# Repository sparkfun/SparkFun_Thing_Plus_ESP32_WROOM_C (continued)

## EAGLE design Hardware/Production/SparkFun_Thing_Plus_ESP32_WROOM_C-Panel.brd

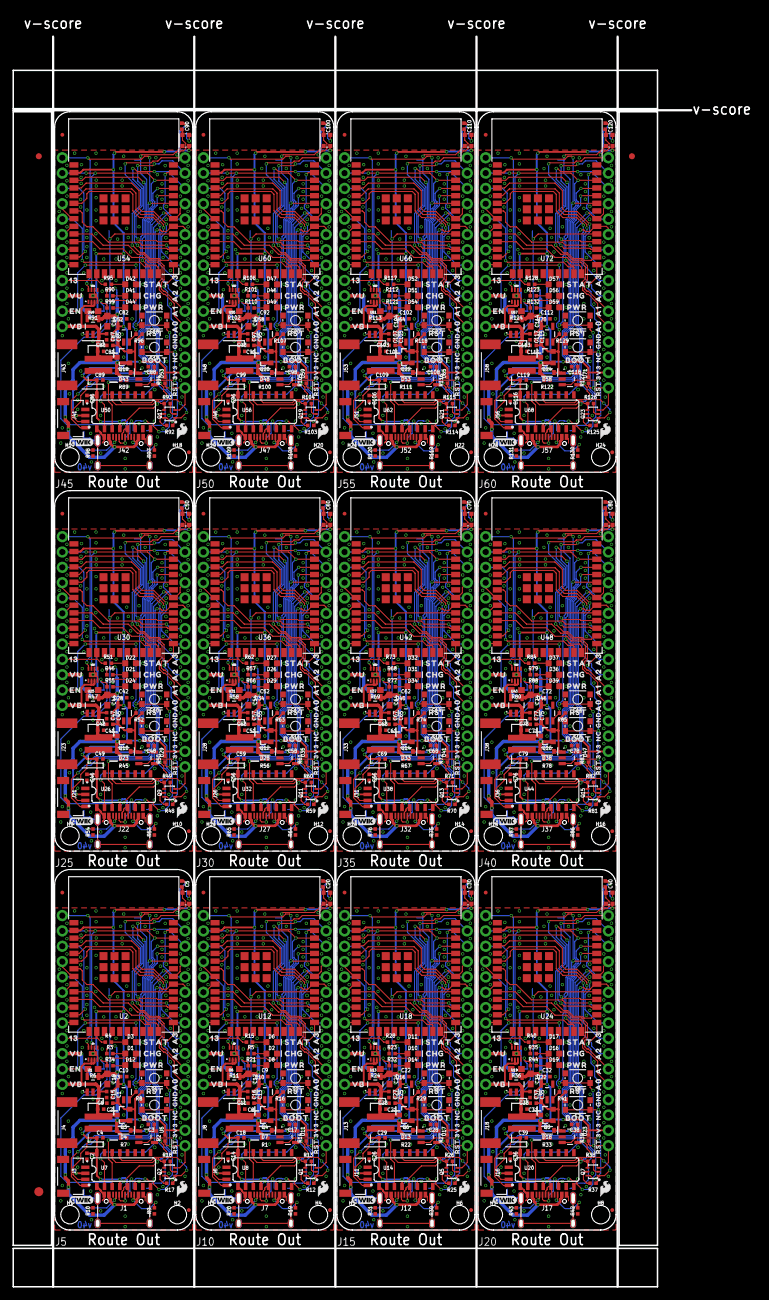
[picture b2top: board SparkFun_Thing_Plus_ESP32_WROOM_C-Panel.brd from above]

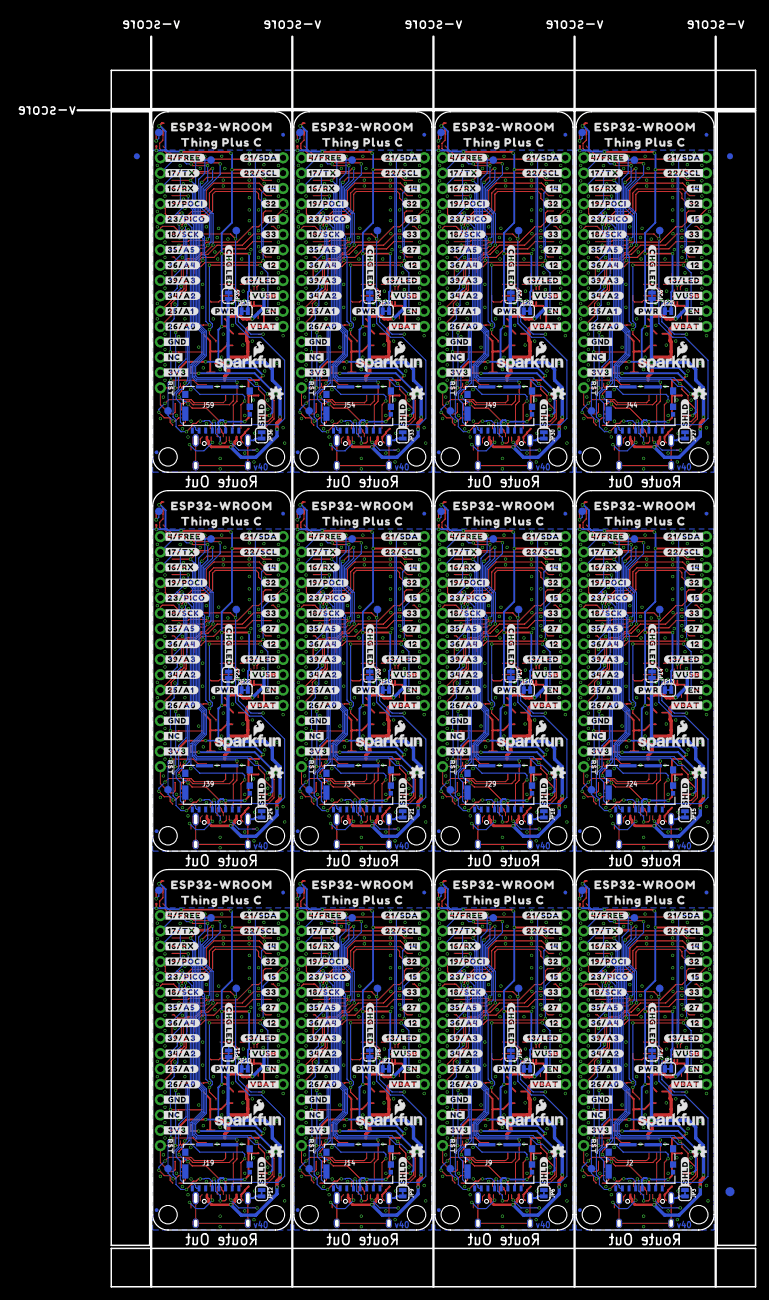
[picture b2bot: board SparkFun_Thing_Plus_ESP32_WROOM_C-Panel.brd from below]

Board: 2 copper layers, 112.3 x 207.0 mm, 1314 parts (555 on the bottom side), 612 nets.

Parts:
C1, C5, C13, C20, C25, C30, C35, C40, C45, C50, C55, C60, C65, C70, C75, C80, C85, C90, C95, C100, C105, C110, C115, C120: 10uF; 0402-TIGHT
C2, C4, C14, C15, C16, C18, C26, C27, C29, C36, C37, C39, C46, C47, C49, C56, C57, C59, C66, C67, C69, C76, C77, C79, C86, C87, C89, C96, C97, C99, C106, C107, C109, C116, C117, C119: 0.1uF; 0402-TIGHT
C3, C7, C8, C9, C10, C17, C21, C22, C28, C31, C32, C38, C41, C42, C48, C51, C52, C58, C61, C62, C68, C71, C72, C78, C81, C82, C88, C91, C92, C98, C101, C102, C108, C111, C112, C118: 1.0uF; 0402-TIGHT
C6, C11, C23, C33, C43, C53, C63, C73, C83, C93, C103, C113: 4.7uF; 0402-TIGHT
C12, C19, C24, C34, C44, C54, C64, C74, C84, C94, C104, C114: 4.7uF; 0603
D1, D2, D10, D16, D21, D26, D31, D36, D41, D46, D51, D56: Yellow; LED-0603
D3, D6, D11, D17, D22, D27, D32, D37, D42, D47, D52, D57: BLUE; LED-0603
D4, D7, D13, D18, D23, D28, D33, D38, D43, D48, D53, D58: 3A/10V/280mV; SOD-323
D5, D9, D15, D20, D25, D30, D35, D40, D45, D50, D55, D60: WS2812; WS2812-2020
D8, D12, D14, D19, D24, D29, D34, D39, D44, D49, D54, D59: RED; LED-0603
E$1, E$2, E$3, E$4: FIDUCIAL-1X2
E$5, E$6: FIDUCIAL-1.5X3
FD1, FD2, FD3, FD4, FD5, FD6, FD7, FD8, FD9, FD10, FD11, FD12, FD13, FD14, FD15, FD16, FD17, FD18, FD19, FD20, FD21, FD22, FD23, FD24, FD25, FD26, FD27, FD28, FD29, FD30, FD31, FD32, FD33, FD34, FD35, FD36, FD37, FD38, FD39, FD40, FD41, FD42, FD43, FD44, FD45, FD46, FD47, FD48: FIDUCIALUFIDUCIAL; FIDUCIAL-MICRO
H1, H2, H3, H4, H5, H6, H7, H8, H9, H10, H11, H12, H13, H14, H15, H16, H17, H18, H19, H20, H21, H22, H23, H24: STAND-OFFTIGHT; STAND-OFF-TIGHT
J1, J7, J12, J17, J22, J27, J32, J37, J42, J47, J52, J57: USB-C-16P-2LAYER-PADS
J2, J9, J14, J19, J24, J29, J34, J39, J44, J49, J54, J59: MICRO-SDFRICTION; MICROSD_TINY
J3, J6, J11, J16, J21, J26, J31, J36, J41, J46, J51, J56: QWIIC_RA; JST04_1MM_RA
J4, J8, J13, J18, J23, J28, J33, J38, J43, J48, J53, J58: JST-2-SMD
J5, J10, J15, J20, J25, J30, J35, J40, J45, J50, J55, J60: THING_PLUS_LOGICAL; THING_PLUS
JP1, JP2, JP3, JP4, JP5, JP6, JP7, JP8, JP9, JP10, JP11, JP12, JP13, JP14, JP15, JP16, JP17, JP18, JP19, JP20, JP21, JP22, JP23, JP24, JP25, JP26, JP27, JP28, JP29, JP30, JP31, JP32, JP33, JP34, JP35, JP36: JUMPER-SMT_2_NC_TRACE_SILK; SMT-JUMPER_2_NC_TRACE_SILK
LOGO1, LOGO6, LOGO9, LOGO12, LOGO15, LOGO18, LOGO21, LOGO24, LOGO27, LOGO30, LOGO33, LOGO36: SFE_LOGO_NAME_FLAME.1_INCH; SFE_LOGO_NAME_FLAME_.1
LOGO2, LOGO3, LOGO7, LOGO10, LOGO13, LOGO16, LOGO19, LOGO22, LOGO25, LOGO28, LOGO31, LOGO34: OSHW-LOGOMINI; OSHW-LOGO-MINI
LOGO4, LOGO5, LOGO8, LOGO11, LOGO14, LOGO17, LOGO20, LOGO23, LOGO26, LOGO29, LOGO32, LOGO35: QWIIC_LOGO_4MM; QWIIC_4MM
Q1, Q2, Q5, Q7, Q9, Q11, Q13, Q15, Q17, Q19, Q21, Q23: MBT3904DW1T1; SC70-6
Q3, Q4, Q6, Q8, Q10, Q12, Q14, Q16, Q18, Q20, Q22, Q24: 20V/4.2A/52mΩ/1.4W; SOT23-3
R1, R2, R7, R8, R12, R13, R14, R16, R17, R18, R22, R25, R26, R27, R29, R33, R37, R38, R39, R41, R45, R48, R49, R50, R52, R56, R59, R60, R61, R63, R67, R70, R71, R72, R74, R78, R81, R82, R83, R85, R89, R92, R93, R94, R96, R100, R103, R104, R105, R107, R111, R114, R115, R116, R118, R122, R125, R126, R127, R129: 10k; 0402-TIGHT
R3, R4, R5, R15, R21, R23, R28, R32, R34, R35, R40, R44, R46, R51, R55, R57, R62, R66, R68, R73, R77, R79, R84, R88, R90, R95, R99, R101, R106, R110, R112, R117, R121, R123, R128, R132: 1k; 0402-TIGHT
R6, R11, R24, R36, R47, R58, R69, R80, R91, R102, R113, R124: 2.0k; 0603
R9, R10, R19, R20, R30, R31, R42, R43, R53, R54, R64, R65, R75, R76, R86, R87, R97, R98, R108, R109, R119, R120, R130, R131: 5.1k; 0402-TIGHT
S1, S3, S5, S7, S9, S11, S13, S15, S17, S19, S21, S23: Boot; TACTILE_SWITCH_SMD_4.6X2.8MM
S2, S4, S6, S8, S10, S12, S14, S16, S18, S20, S22, S24: Reset; TACTILE_SWITCH_SMD_4.6X2.8MM
TP1, TP2, TP3, TP4, TP5, TP6, TP7, TP8, TP9, TP10, TP11, TP12, TP13, TP14, TP15, TP16, TP17, TP18, TP19, TP20, TP21, TP22, TP23, TP24, TP25, TP26, TP27, TP28, TP29, TP30, TP31, TP32, TP33, TP34, TP35, TP36, TP37, TP38, TP39, TP40, TP41, TP42, TP43, TP44, TP45, TP46, TP47, TP48: TEST-POINT3X5; PAD.03X.05
U1, U6, U13, U19, U25, U31, U37, U43, U49, U55, U61, U67: MCP73831; SOT23-5
U2, U12, U18, U24, U30, U36, U42, U48, U54, U60, U66, U72: ESP-WROOM-3232D-NARROW; ESP-WROOM-32D-NARROW
U3, U5, U10, U11, U16, U17, U22, U23, U28, U29, U34, U35, U40, U41, U46, U47, U52, U53, U58, U59, U64, U65, U70, U71: XC6222B331MR-G; SOT23-5
U4, U9, U15, U21, U27, U33, U39, U45, U51, U57, U63, U69: MAX17048; DFN-8
U7, U8, U14, U20, U26, U32, U38, U44, U50, U56, U62, U68: CH340C; SO016
U$1, U$57, U$145, U$197, U$249, U$301, U$353, U$405, U$457, U$509, U$561, U$613: SFE_LOGO_FLAME_STOP_.1
U$2, U$58, U$146, U$198, U$250, U$302, U$354, U$406, U$458, U$510, U$562, U$614: #23#PICO#0
U$3, U$59, U$147, U$199, U$251, U$303, U$355, U$407, U$459, U$511, U$563, U$615: #19#POCI#0
U$4, U$60, U$148, U$200, U$252, U$304, U$356, U$408, U$460, U$512, U$564, U$616: #4#FREE#0
U$5, U$61, U$149, U$201, U$253, U$305, U$357, U$409, U$461, U$513, U$565, U$617: #CHG_LED#0
U$6, U$62, U$150, U$202, U$254, U$306, U$358, U$410, U$462, U$514, U$566, U$618: ESP32#WROOM0
U$7, U$63, U$151, U$203, U$255, U$307, U$359, U$411, U$463, U$515, U$567, U$619: THING_PLUS_C0
U$8, U$82, U$156, U$208, U$260, U$312, U$364, U$416, U$468, U$520, U$572, U$624: #SHLD#0
U$9, U$64, U$152, U$204, U$256, U$308, U$360, U$412, U$464, U$516, U$568, U$620: #_GND#0
U$10, U$65, U$153, U$205, U$257, U$309, U$361, U$413, U$465, U$517, U$569, U$621: #_NC#0
U$11, U$66, U$154, U$206, U$258, U$310, U$362, U$414, U$466, U$518, U$570, U$622: #_3V3#0
U$12, U$67, U$155, U$207, U$259, U$311, U$363, U$415, U$467, U$519, U$571, U$623: SFE_LOGO_FLAME_.1
U$13, U$24, U$103, U$157, U$209, U$261, U$313, U$365, U$417, U$469, U$521, U$573: CHG1
U$14, U$25, U$104, U$158, U$210, U$262, U$314, U$366, U$418, U$470, U$522, U$574: PWR2
U$15, U$26, U$105, U$159, U$211, U$263, U$315, U$367, U$419, U$471, U$523, U$575: STAT0
U$16, U$68, U$106, U$160, U$212, U$264, U$316, U$368, U$420, U$472, U$524, U$576: A03
U$17, U$69, U$108, U$161, U$213, U$265, U$317, U$369, U$421, U$473, U$525, U$577: A12
U$18, U$70, U$110, U$162, U$214, U$266, U$318, U$370, U$422, U$474, U$526, U$578: A21
U$19, U$71, U$111, U$163, U$215, U$267, U$319, U$371, U$423, U$475, U$527, U$579: A30
U$20, U$74, U$112, U$164, U$216, U$268, U$320, U$372, U$424, U$476, U$528, U$580: EN3
U$21, U$77, U$113, U$165, U$217, U$269, U$321, U$373, U$425, U$477, U$529, U$581: 130
U$22, U$78, U$114, U$166, U$218, U$270, U$322, U$374, U$426, U$478, U$530, U$582: BOOT0
U$23, U$31, U$119, U$171, U$223, U$275, U$327, U$379, U$431, U$483, U$535, U$587: 3V30
U$27, U$54, U$79, U$109, U$115, U$142, U$167, U$194, U$219, U$246, U$271, U$298, U$323, U$350, U$375, U$402, U$427, U$454, U$479, U$506, U$531, U$558, U$583, U$610: #RST#0
U$28, U$80, U$116, U$168, U$220, U$272, U$324, U$376, U$428, U$480, U$532, U$584: RST0
U$29, U$73, U$117, U$169, U$221, U$273, U$325, U$377, U$429, U$481, U$533, U$585: VB1
U$30, U$76, U$118, U$170, U$222, U$274, U$326, U$378, U$430, U$482, U$534, U$586: VU0
U$32, U$72, U$120, U$172, U$224, U$276, U$328, U$380, U$432, U$484, U$536, U$588: #17#TX#0
U$33, U$81, U$121, U$173, U$225, U$277, U$329, U$381, U$433, U$485, U$537, U$589: #16#RX#0
U$34, U$83, U$122, U$174, U$226, U$278, U$330, U$382, U$434, U$486, U$538, U$590: #18#SCK#0
U$35, U$84, U$123, U$175, U$227, U$279, U$331, U$383, U$435, U$487, U$539, U$591: #35#A5#0
U$36, U$85, U$124, U$176, U$228, U$280, U$332, U$384, U$436, U$488, U$540, U$592: #36#A4#0
U$37, U$86, U$125, U$177, U$229, U$281, U$333, U$385, U$437, U$489, U$541, U$593: #25#A1#2
U$38, U$87, U$126, U$178, U$230, U$282, U$334, U$386, U$438, U$490, U$542, U$594: #26#A0#3
U$39, U$88, U$127, U$179, U$231, U$283, U$335, U$387, U$439, U$491, U$543, U$595: #34#A2#1
U$40, U$89, U$128, U$180, U$232, U$284, U$336, U$388, U$440, U$492, U$544, U$596: #39#A3#0
U$41, U$90, U$129, U$181, U$233, U$285, U$337, U$389, U$441, U$493, U$545, U$597: #12#4
U$42, U$91, U$130, U$182, U$234, U$286, U$338, U$390, U$442, U$494, U$546, U$598: #14#9
U$43, U$92, U$131, U$183, U$235, U$287, U$339, U$391, U$443, U$495, U$547, U$599: #15#7
U$44, U$93, U$132, U$184, U$236, U$288, U$340, U$392, U$444, U$496, U$548, U$600: #27#5
U$45, U$94, U$133, U$185, U$237, U$289, U$341, U$393, U$445, U$497, U$549, U$601: #32#8
U$46, U$95, U$134, U$186, U$238, U$290, U$342, U$394, U$446, U$498, U$550, U$602: #33#6
U$47, U$96, U$135, U$187, U$239, U$291, U$343, U$395, U$447, U$499, U$551, U$603: #EN#1
U$48, U$97, U$136, U$188, U$240, U$292, U$344, U$396, U$448, U$500, U$552, U$604: #VBAT#0
U$49, U$98, U$137, U$189, U$241, U$293, U$345, U$397, U$449, U$501, U$553, U$605: #VUSB#2
U$50, U$99, U$138, U$190, U$242, U$294, U$346, U$398, U$450, U$502, U$554, U$606: #13#LED#0
U$51, U$100, U$139, U$191, U$243, U$295, U$347, U$399, U$451, U$503, U$555, U$607: #21#SDA#1
U$52, U$101, U$140, U$192, U$244, U$296, U$348, U$400, U$452, U$504, U$556, U$608: #22#SCL#0
U$53, U$102, U$141, U$193, U$245, U$297, U$349, U$401, U$453, U$505, U$557, U$609: #PWR#0
U$55, U$75, U$143, U$195, U$247, U$299, U$351, U$403, U$455, U$507, U$559, U$611: GND1
U$56, U$107, U$144, U$196, U$248, U$300, U$352, U$404, U$456, U$508, U$560, U$612: NC0

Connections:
3.3V: C1.1, C2.1, C4.1, C5.1, C10.1, D5.VCC, J2.4, J5.27, JP1.2, R2.2, U2.2, U3.5, U7.4, U7.16
3.3V1: C9.1, C13.1, C14.1, C18.1, C20.1, D9.VCC, J9.4, J10.27, JP4.2, R14.2, U8.4, U8.16, U10.5, U12.2
3.3V2: C22.1, C25.1, C26.1, C29.1, C30.1, D15.VCC, J14.4, J15.27, JP7.2, R27.2, U14.4, U14.16, U16.5, U18.2
3.3V3: C32.1, C35.1, C36.1, C39.1, C40.1, D20.VCC, J19.4, J20.27, JP10.2, R39.2, U20.4, U20.16, U22.5, U24.2
3.3V4: C42.1, C45.1, C46.1, C49.1, C50.1, D25.VCC, J24.4, J25.27, JP13.2, R50.2, U26.4, U26.16, U28.5, U30.2
3.3V5: C52.1, C55.1, C56.1, C59.1, C60.1, D30.VCC, J29.4, J30.27, JP16.2, R61.2, U32.4, U32.16, U34.5, U36.2
3.3V6: C62.1, C65.1, C66.1, C69.1, C70.1, D35.VCC, J34.4, J35.27, JP19.2, R72.2, U38.4, U38.16, U40.5, U42.2
3.3V7: C72.1, C75.1, C76.1, C79.1, C80.1, D40.VCC, J39.4, J40.27, JP22.2, R83.2, U44.4, U44.16, U46.5, U48.2
3.3V8: C82.1, C85.1, C86.1, C89.1, C90.1, D45.VCC, J44.4, J45.27, JP25.2, R94.2, U50.4, U50.16, U52.5, U54.2
3.3V9: C92.1, C95.1, C96.1, C99.1, C100.1, D50.VCC, J49.4, J50.27, JP28.2, R105.2, U56.4, U56.16, U58.5, U60.2
3.3V10: C102.1, C105.1, C106.1, C109.1, C110.1, D55.VCC, J54.4, J55.27, JP31.2, R116.2, U62.4, U62.16, U64.5, U66.2
3.3V11: C112.1, C115.1, C116.1, C119.1, C120.1, D60.VCC, J59.4, J60.27, JP34.2, R127.2, U68.4, U68.16, U70.5, U72.2
!RESET!: J5.28, Q2.3, R2.1, S4.3, S4.4, U2.3
!RESET!1: J10.28, Q1.3, R14.1, S2.3, S2.4, U12.3
!RESET!2: J15.28, Q5.3, R27.1, S6.3, S6.4, U18.3
!RESET!3: J20.28, Q7.3, R39.1, S8.3, S8.4, U24.3
!RESET!4: J25.28, Q9.3, R50.1, S10.3, S10.4, U30.3
!RESET!5: J30.28, Q11.3, R61.1, S12.3, S12.4, U36.3
!RESET!6: J35.28, Q13.3, R72.1, S14.3, S14.4, U42.3
!RESET!7: J40.28, Q15.3, R83.1, S16.3, S16.4, U48.3
!RESET!8: J45.28, Q17.3, R94.1, S18.3, S18.4, U54.3
!RESET!9: J50.28, Q19.3, R105.1, S20.3, S20.4, U60.3
!RESET!10: J55.28, Q21.3, R116.1, S22.3, S22.4, U66.3
!RESET!11: J60.28, Q23.3, R127.1, S24.3, S24.4, U72.3
CH340-DTR: Q2.1, R17.1, U7.13
CH340-DTR1: Q1.1, R12.1, U8.13
CH340-DTR2: Q5.1, R25.1, U14.13
CH340-DTR3: Q7.1, R37.1, U20.13
CH340-DTR4: Q9.1, R48.1, U26.13
CH340-DTR5: Q11.1, R59.1, U32.13
CH340-DTR6: Q13.1, R70.1, U38.13
CH340-DTR7: Q15.1, R81.1, U44.13
CH340-DTR8: Q17.1, R92.1, U50.13
CH340-DTR9: Q19.1, R103.1, U56.13
CH340-DTR10: Q21.1, R114.1, U62.13
CH340-DTR11: Q23.1, R125.1, U68.13
CH340-RTS: Q2.4, R18.1, U7.14
CH340-RTS1: Q1.4, R13.1, U8.14
CH340-RTS2: Q5.4, R26.1, U14.14
CH340-RTS3: Q7.4, R38.1, U20.14
CH340-RTS4: Q9.4, R49.1, U26.14
CH340-RTS5: Q11.4, R60.1, U32.14
CH340-RTS6: Q13.4, R71.1, U38.14
CH340-RTS7: Q15.4, R82.1, U44.14
CH340-RTS8: Q17.4, R93.1, U50.14
CH340-RTS9: Q19.4, R104.1, U56.14
CH340-RTS10: Q21.4, R115.1, U62.14
CH340-RTS11: Q23.4, R126.1, U68.14
CH340-RX: U2.35, U7.3
CH340-RX1: U8.3, U12.35
CH340-RX2: U14.3, U18.35
CH340-RX3: U20.3, U24.35
CH340-RX4: U26.3, U30.35
CH340-RX5: U32.3, U36.35
CH340-RX6: U38.3, U42.35
CH340-RX7: U44.3, U48.35
CH340-RX8: U50.3, U54.35
CH340-RX9: U56.3, U60.35
CH340-RX10: U62.3, U66.35
CH340-RX11: U68.3, U72.35
CH340-TX: U2.34, U7.2
CH340-TX1: U8.2, U12.34
CH340-TX2: U14.2, U18.34
CH340-TX3: U20.2, U24.34
CH340-TX4: U26.2, U30.34
CH340-TX5: U32.2, U36.34
CH340-TX6: U38.2, U42.34
CH340-TX7: U44.2, U48.34
CH340-TX8: U50.2, U54.34
CH340-TX9: U56.2, U60.34
CH340-TX10: U62.2, U66.34
CH340-TX11: U68.2, U72.34
CHG_LED: D1.A, R3.2
CHG_LED1: D2.A, R5.2
CHG_LED2: D10.A, R23.2
CHG_LED3: D16.A, R35.2
CHG_LED4: D21.A, R46.2
CHG_LED5: D26.A, R57.2
CHG_LED6: D31.A, R68.2
CHG_LED7: D36.A, R79.2
CHG_LED8: D41.A, R90.2
CHG_LED9: D46.A, R101.2
CHG_LED10: D51.A, R112.2
CHG_LED11: D56.A, R123.2
D+: J1.A6, J1.B6, U7.5
D+1: J7.A6, J7.B6, U8.5
D+2: J12.A6, J12.B6, U14.5
D+3: J17.A6, J17.B6, U20.5
D+4: J22.A6, J22.B6, U26.5
D+5: J27.A6, J27.B6, U32.5
D+6: J32.A6, J32.B6, U38.5
D+7: J37.A6, J37.B6, U44.5
D+8: J42.A6, J42.B6, U50.5
D+9: J47.A6, J47.B6, U56.5
D+10: J52.A6, J52.B6, U62.5
D+11: J57.A6, J57.B6, U68.5
D-: J1.A7, J1.B7, U7.6
D-1: J7.A7, J7.B7, U8.6
D-2: J12.A7, J12.B7, U14.6
D-3: J17.A7, J17.B7, U20.6
D-4: J22.A7, J22.B7, U26.6
D-5: J27.A7, J27.B7, U32.6
D-6: J32.A7, J32.B7, U38.6
D-7: J37.A7, J37.B7, U44.6
D-8: J42.A7, J42.B7, U50.6
D-9: J47.A7, J47.B7, U56.6
D-10: J52.A7, J52.B7, U62.6
D-11: J57.A7, J57.B7, U68.6
DTR-10K: Q2.5, R17.2
DTR-10K1: Q1.5, R12.2
DTR-10K2: Q5.5, R25.2
DTR-10K3: Q7.5, R37.2
DTR-10K4: Q9.5, R48.2
DTR-10K5: Q11.5, R59.2
DTR-10K6: Q13.5, R70.2
DTR-10K7: Q15.5, R81.2
DTR-10K8: Q17.5, R92.2
DTR-10K9: Q19.5, R103.2
DTR-10K10: Q21.5, R114.2
DTR-10K11: Q23.5, R125.2
ESP_0/QPWR: Q2.6, S3.3, S3.4, TP1.1, U2.25, U5.3
ESP_0/QPWR1: Q1.6, S1.3, S1.4, TP5.1, U11.3, U12.25
ESP_0/QPWR2: Q5.6, S5.3, S5.4, TP9.1, U17.3, U18.25
ESP_0/QPWR3: Q7.6, S7.3, S7.4, TP13.1, U23.3, U24.25
ESP_0/QPWR4: Q9.6, S9.3, S9.4, TP17.1, U29.3, U30.25
ESP_0/QPWR5: Q11.6, S11.3, S11.4, TP21.1, U35.3, U36.25
ESP_0/QPWR6: Q13.6, S13.3, S13.4, TP25.1, U41.3, U42.25
ESP_0/QPWR7: Q15.6, S15.3, S15.4, TP29.1, U47.3, U48.25
ESP_0/QPWR8: Q17.6, S17.3, S17.4, TP33.1, U53.3, U54.25
ESP_0/QPWR9: Q19.6, S19.3, S19.4, TP37.1, U59.3, U60.25
ESP_0/QPWR10: Q21.6, S21.3, S21.4, TP41.1, U65.3, U66.25
ESP_0/QPWR11: Q23.6, S23.3, S23.4, TP45.1, U71.3, U72.25
ESP_2/RGB_DI: D5.DI, TP3.1, U2.24
ESP_2/RGB_DI1: D9.DI, TP7.1, U12.24
ESP_2/RGB_DI2: D15.DI, TP11.1, U18.24
ESP_2/RGB_DI3: D20.DI, TP15.1, U24.24
ESP_2/RGB_DI4: D25.DI, TP19.1, U30.24
ESP_2/RGB_DI5: D30.DI, TP23.1, U36.24
ESP_2/RGB_DI6: D35.DI, TP27.1, U42.24
ESP_2/RGB_DI7: D40.DI, TP31.1, U48.24
ESP_2/RGB_DI8: D45.DI, TP35.1, U54.24
ESP_2/RGB_DI9: D50.DI, TP39.1, U60.24
ESP_2/RGB_DI10: D55.DI, TP43.1, U66.24
ESP_2/RGB_DI11: D60.DI, TP47.1, U72.24
ESP_4/TP_FB: J5.13, U2.26
ESP_4/TP_FB1: J10.13, U12.26
ESP_4/TP_FB2: J15.13, U18.26
ESP_4/TP_FB3: J20.13, U24.26
ESP_4/TP_FB4: J25.13, U30.26
ESP_4/TP_FB5: J30.13, U36.26
ESP_4/TP_FB6: J35.13, U42.26
ESP_4/TP_FB7: J40.13, U48.26
ESP_4/TP_FB8: J45.13, U54.26
ESP_4/TP_FB9: J50.13, U60.26
ESP_4/TP_FB10: J55.13, U66.26
ESP_4/TP_FB11: J60.13, U72.26
ESP_5/SD_CS: J2.2, TP4.1, U2.29
ESP_5/SD_CS1: J9.2, TP8.1, U12.29
ESP_5/SD_CS2: J14.2, TP12.1, U18.29
ESP_5/SD_CS3: J19.2, TP16.1, U24.29
ESP_5/SD_CS4: J24.2, TP20.1, U30.29
ESP_5/SD_CS5: J29.2, TP24.1, U36.29
ESP_5/SD_CS6: J34.2, TP28.1, U42.29
ESP_5/SD_CS7: J39.2, TP32.1, U48.29
ESP_5/SD_CS8: J44.2, TP36.1, U54.29
ESP_5/SD_CS9: J49.2, TP40.1, U60.29
ESP_5/SD_CS10: J54.2, TP44.1, U66.29
ESP_5/SD_CS11: J59.2, TP48.1, U72.29
ESP_12/GPIO1: J5.8, U2.14
ESP_12/GPIO2: J10.8, U12.14
ESP_12/GPIO3: J15.8, U18.14
ESP_12/GPIO4: J20.8, U24.14
ESP_12/GPIO5: J25.8, U30.14
ESP_12/GPIO6: J30.8, U36.14
ESP_12/GPIO7: J35.8, U42.14
ESP_12/GPIO8: J40.8, U48.14
ESP_12/GPIO9: J45.8, U54.14
ESP_12/GPIO10: J50.8, U60.14
ESP_12/GPIO11: J55.8, U66.14
ESP_12/GPIO12: J60.8, U72.14
ESP_13/GPIO0/LED: J5.9, R4.1, U2.16
ESP_13/GPIO0/LED1: J10.9, R15.1, U12.16
ESP_13/GPIO0/LED2: J15.9, R28.1, U18.16
ESP_13/GPIO0/LED3: J20.9, R40.1, U24.16
ESP_13/GPIO0/LED4: J25.9, R51.1, U30.16
ESP_13/GPIO0/LED5: J30.9, R62.1, U36.16
ESP_13/GPIO0/LED6: J35.9, R73.1, U42.16
ESP_13/GPIO0/LED7: J40.9, R84.1, U48.16
ESP_13/GPIO0/LED8: J45.9, R95.1, U54.16
ESP_13/GPIO0/LED9: J50.9, R106.1, U60.16
ESP_13/GPIO0/LED10: J55.9, R117.1, U66.16
ESP_13/GPIO0/LED11: J60.9, R128.1, U72.16
ESP_14/GPIO1: J10.3, U12.13
ESP_14/GPIO2: J15.3, U18.13
ESP_14/GPIO3: J20.3, U24.13
ESP_14/GPIO4: J25.3, U30.13
ESP_14/GPIO5: J30.3, U36.13
ESP_14/GPIO6: J5.3, U2.13
ESP_14/GPIO7: J35.3, U42.13
ESP_14/GPIO8: J40.3, U48.13
ESP_14/GPIO9: J45.3, U54.13
ESP_14/GPIO10: J50.3, U60.13
ESP_14/GPIO11: J55.3, U66.13
ESP_14/GPIO12: J60.3, U72.13
ESP_15/GPIO1: J10.5, U12.23
ESP_15/GPIO2: J15.5, U18.23
ESP_15/GPIO3: J20.5, U24.23
ESP_15/GPIO4: J5.5, U2.23
ESP_15/GPIO5: J25.5, U30.23
ESP_15/GPIO6: J30.5, U36.23
ESP_15/GPIO7: J35.5, U42.23
ESP_15/GPIO8: J40.5, U48.23
ESP_15/GPIO9: J45.5, U54.23
ESP_15/GPIO10: J50.5, U60.23
ESP_15/GPIO11: J55.5, U66.23
ESP_15/GPIO12: J60.5, U72.23
ESP_16/TP_RX: J5.15, U2.27
ESP_16/TP_RX1: J10.15, U12.27
ESP_16/TP_RX2: J15.15, U18.27
ESP_16/TP_RX3: J20.15, U24.27
ESP_16/TP_RX4: J25.15, U30.27
ESP_16/TP_RX5: J30.15, U36.27
ESP_16/TP_RX6: J35.15, U42.27
ESP_16/TP_RX7: J40.15, U48.27
ESP_16/TP_RX8: J45.15, U54.27
ESP_16/TP_RX9: J50.15, U60.27
ESP_16/TP_RX10: J55.15, U66.27
ESP_16/TP_RX11: J60.15, U72.27
ESP_17/TP_TX: J5.14, U2.28
ESP_17/TP_TX1: J10.14, U12.28
ESP_17/TP_TX2: J15.14, U18.28
ESP_17/TP_TX3: J20.14, U24.28
ESP_17/TP_TX4: J25.14, U30.28
ESP_17/TP_TX5: J30.14, U36.28
ESP_17/TP_TX6: J35.14, U42.28
ESP_17/TP_TX7: J40.14, U48.28
ESP_17/TP_TX8: J45.14, U54.28
ESP_17/TP_TX9: J50.14, U60.28
ESP_17/TP_TX10: J55.14, U66.28
ESP_17/TP_TX11: J60.14, U72.28
ESP_18/TP_SCK: J2.5, J5.18, U2.30
ESP_18/TP_SCK1: J9.5, J10.18, U12.30
ESP_18/TP_SCK2: J14.5, J15.18, U18.30
ESP_18/TP_SCK3: J19.5, J20.18, U24.30
ESP_18/TP_SCK4: J24.5, J25.18, U30.30
ESP_18/TP_SCK5: J29.5, J30.18, U36.30
ESP_18/TP_SCK6: J34.5, J35.18, U42.30
ESP_18/TP_SCK7: J39.5, J40.18, U48.30
ESP_18/TP_SCK8: J44.5, J45.18, U54.30
ESP_18/TP_SCK9: J49.5, J50.18, U60.30
ESP_18/TP_SCK10: J54.5, J55.18, U66.30
ESP_18/TP_SCK11: J59.5, J60.18, U72.30
ESP_19/TP_POCI: J2.7, J5.16, U2.31
ESP_19/TP_POCI1: J9.7, J10.16, U12.31
ESP_19/TP_POCI2: J14.7, J15.16, U18.31
ESP_19/TP_POCI3: J19.7, J20.16, U24.31
ESP_19/TP_POCI4: J24.7, J25.16, U30.31
ESP_19/TP_POCI5: J29.7, J30.16, U36.31
ESP_19/TP_POCI6: J34.7, J35.16, U42.31
ESP_19/TP_POCI7: J39.7, J40.16, U48.31
ESP_19/TP_POCI8: J44.7, J45.16, U54.31
ESP_19/TP_POCI9: J49.7, J50.16, U60.31
ESP_19/TP_POCI10: J54.7, J55.16, U66.31
ESP_19/TP_POCI11: J59.7, J60.16, U72.31
ESP_21/TP_SDA: J3.3, J5.1, U2.33, U4.8
ESP_21/TP_SDA1: J6.3, J10.1, U9.8, U12.33
ESP_21/TP_SDA2: J11.3, J15.1, U15.8, U18.33
ESP_21/TP_SDA3: J16.3, J20.1, U21.8, U24.33
ESP_21/TP_SDA4: J21.3, J25.1, U27.8, U30.33
ESP_21/TP_SDA5: J26.3, J30.1, U33.8, U36.33
ESP_21/TP_SDA6: J31.3, J35.1, U39.8, U42.33
ESP_21/TP_SDA7: J36.3, J40.1, U45.8, U48.33
ESP_21/TP_SDA8: J41.3, J45.1, U51.8, U54.33
ESP_21/TP_SDA9: J46.3, J50.1, U57.8, U60.33
ESP_21/TP_SDA10: J51.3, J55.1, U63.8, U66.33
ESP_21/TP_SDA11: J56.3, J60.1, U69.8, U72.33
ESP_22/TP_SCL: J3.4, J5.2, U2.36, U4.7
ESP_22/TP_SCL1: J6.4, J10.2, U9.7, U12.36
ESP_22/TP_SCL2: J11.4, J15.2, U15.7, U18.36
ESP_22/TP_SCL3: J16.4, J20.2, U21.7, U24.36
ESP_22/TP_SCL4: J21.4, J25.2, U27.7, U30.36
ESP_22/TP_SCL5: J26.4, J30.2, U33.7, U36.36
ESP_22/TP_SCL6: J31.4, J35.2, U39.7, U42.36
ESP_22/TP_SCL7: J36.4, J40.2, U45.7, U48.36
ESP_22/TP_SCL8: J41.4, J45.2, U51.7, U54.36
ESP_22/TP_SCL9: J46.4, J50.2, U57.7, U60.36
ESP_22/TP_SCL10: J51.4, J55.2, U63.7, U66.36
ESP_22/TP_SCL11: J56.4, J60.2, U69.7, U72.36
ESP_23/TP_PICO: J2.3, J5.17, U2.37
ESP_23/TP_PICO1: J9.3, J10.17, U12.37
ESP_23/TP_PICO2: J14.3, J15.17, U18.37
ESP_23/TP_PICO3: J19.3, J20.17, U24.37
ESP_23/TP_PICO4: J24.3, J25.17, U30.37
ESP_23/TP_PICO5: J29.3, J30.17, U36.37
ESP_23/TP_PICO6: J34.3, J35.17, U42.37
ESP_23/TP_PICO7: J39.3, J40.17, U48.37
ESP_23/TP_PICO8: J44.3, J45.17, U54.37
ESP_23/TP_PICO9: J49.3, J50.17, U60.37
ESP_23/TP_PICO10: J54.3, J55.17, U66.37
ESP_23/TP_PICO11: J59.3, J60.17, U72.37
ESP_25/TP_A1: J5.23, U2.10
ESP_25/TP_A2: J10.23, U12.10
ESP_25/TP_A3: J15.23, U18.10
ESP_25/TP_A4: J20.23, U24.10
ESP_25/TP_A5: J25.23, U30.10
ESP_25/TP_A6: J30.23, U36.10
ESP_25/TP_A7: J35.23, U42.10
ESP_25/TP_A8: J40.23, U48.10
ESP_25/TP_A9: J45.23, U54.10
ESP_25/TP_A10: J50.23, U60.10
ESP_25/TP_A11: J55.23, U66.10
ESP_25/TP_A12: J60.23, U72.10
ESP_26/TP_A0: J5.24, U2.11
ESP_26/TP_A1: J10.24, U12.11
ESP_26/TP_A2: J15.24, U18.11
ESP_26/TP_A3: J20.24, U24.11
ESP_26/TP_A4: J25.24, U30.11
ESP_26/TP_A5: J30.24, U36.11
ESP_26/TP_A6: J35.24, U42.11
ESP_26/TP_A7: J40.24, U48.11
ESP_26/TP_A8: J45.24, U54.11
ESP_26/TP_A9: J50.24, U60.11
ESP_26/TP_A10: J55.24, U66.11
ESP_26/TP_A11: J60.24, U72.11
ESP_27/GPIO1: J10.7, U12.12
ESP_27/GPIO2: J5.7, U2.12
ESP_27/GPIO3: J15.7, U18.12
ESP_27/GPIO4: J20.7, U24.12
ESP_27/GPIO5: J25.7, U30.12
ESP_27/GPIO6: J30.7, U36.12
ESP_27/GPIO7: J35.7, U42.12
ESP_27/GPIO8: J40.7, U48.12
ESP_27/GPIO9: J45.7, U54.12
ESP_27/GPIO10: J50.7, U60.12
ESP_27/GPIO11: J55.7, U66.12
ESP_27/GPIO12: J60.7, U72.12
ESP_32/GPIO1: J10.4, U12.8
ESP_32/GPIO2: J15.4, U18.8
ESP_32/GPIO3: J20.4, U24.8
ESP_32/GPIO4: J25.4, U30.8
ESP_32/GPIO5: J5.4, U2.8
ESP_32/GPIO6: J30.4, U36.8
ESP_32/GPIO7: J35.4, U42.8
ESP_32/GPIO8: J40.4, U48.8
ESP_32/GPIO9: J45.4, U54.8
ESP_32/GPIO10: J50.4, U60.8
ESP_32/GPIO11: J55.4, U66.8
ESP_32/GPIO12: J60.4, U72.8
ESP_33/GPIO1: J10.6, U12.9
ESP_33/GPIO2: J15.6, U18.9
ESP_33/GPIO3: J5.6, U2.9
ESP_33/GPIO4: J20.6, U24.9
ESP_33/GPIO5: J25.6, U30.9
ESP_33/GPIO6: J30.6, U36.9
ESP_33/GPIO7: J35.6, U42.9
ESP_33/GPIO8: J40.6, U48.9
ESP_33/GPIO9: J45.6, U54.9
ESP_33/GPIO10: J50.6, U60.9
ESP_33/GPIO11: J55.6, U66.9
ESP_33/GPIO12: J60.6, U72.9
ESP_34/TP_A1: J10.22, U12.6
ESP_34/TP_A2: J5.22, U2.6
ESP_34/TP_A3: J15.22, U18.6
ESP_34/TP_A4: J20.22, U24.6
ESP_34/TP_A5: J25.22, U30.6
ESP_34/TP_A6: J30.22, U36.6
ESP_34/TP_A7: J35.22, U42.6
ESP_34/TP_A8: J40.22, U48.6
ESP_34/TP_A9: J45.22, U54.6
ESP_34/TP_A10: J50.22, U60.6
ESP_34/TP_A11: J55.22, U66.6
ESP_34/TP_A12: J60.22, U72.6
ESP_35/TP_A1: J10.19, U12.7
ESP_35/TP_A2: J15.19, U18.7
ESP_35/TP_A3: J20.19, U24.7
ESP_35/TP_A4: J25.19, U30.7
ESP_35/TP_A5: J5.19, U2.7
ESP_35/TP_A6: J30.19, U36.7
ESP_35/TP_A7: J35.19, U42.7
ESP_35/TP_A8: J40.19, U48.7
ESP_35/TP_A9: J45.19, U54.7
ESP_35/TP_A10: J50.19, U60.7
ESP_35/TP_A11: J55.19, U66.7
ESP_35/TP_A12: J60.19, U72.7
ESP_36/TP_A1: J10.20, U12.4
ESP_36/TP_A2: J15.20, U18.4
ESP_36/TP_A3: J20.20, U24.4
ESP_36/TP_A4: J5.20, U2.4
ESP_36/TP_A5: J25.20, U30.4
ESP_36/TP_A6: J30.20, U36.4
ESP_36/TP_A7: J35.20, U42.4
ESP_36/TP_A8: J40.20, U48.4
ESP_36/TP_A9: J45.20, U54.4
ESP_36/TP_A10: J50.20, U60.4
ESP_36/TP_A11: J55.20, U66.4
ESP_36/TP_A12: J60.20, U72.4
ESP_39/TP_A1: J10.21, U12.5
ESP_39/TP_A2: J15.21, U18.5
ESP_39/TP_A3: J5.21, U2.5
ESP_39/TP_A4: J20.21, U24.5
ESP_39/TP_A5: J25.21, U30.5
ESP_39/TP_A6: J30.21, U36.5
ESP_39/TP_A7: J35.21, U42.5
ESP_39/TP_A8: J40.21, U48.5
ESP_39/TP_A9: J45.21, U54.5
ESP_39/TP_A10: J50.21, U60.5
ESP_39/TP_A11: J55.21, U66.5
ESP_39/TP_A12: J60.21, U72.5
GND: C1.2, C2.2, C3.2, C4.2, C5.2, C6.2, C7.2, C10.2, C15.2, C19.2, D3.C, D5.GND, D12.C, J1.GND, J1.GND2, J2.6, J2.GND1, J2.GND2, J2.GND3, J2.GND4, J2.GND5, J2.GND6, J3.1, J4.1, J5.25, JP3.1, R6.1, R7.1, R9.1, R10.1, S3.1, S3.2, S4.1, S4.2, U1.2, U2.1, U2.15, U2.38, U2.GND1, U2.GNDT1, U2.GNDT2, U2.GNDT3, U2.GNDT4, U2.GNDT5, U2.GNDT6, U2.GNDT7, U2.GNDT8, U3.2, U4.1, U4.4, U4.6, U4.9, U5.2, U7.1
GND1: C8.2, C9.2, C11.2, C12.2, C13.2, C14.2, C16.2, C17.2, C18.2, C20.2, D6.C, D8.C, D9.GND, J6.1, J7.GND, J7.GND2, J8.1, J9.6, J9.GND1, J9.GND2, J9.GND3, J9.GND4, J9.GND5, J9.GND6, J10.25, JP6.1, R1.1, R11.1, R19.1, R20.1, S1.1, S1.2, S2.1, S2.2, U6.2, U8.1, U9.1, U9.4, U9.6, U9.9, U10.2, U11.2, U12.1, U12.15, U12.38, U12.GND1, U12.GNDT1, U12.GNDT2, U12.GNDT3, U12.GNDT4, U12.GNDT5, U12.GNDT6, U12.GNDT7, U12.GNDT8
GND2: C21.2, C22.2, C23.2, C24.2, C25.2, C26.2, C27.2, C28.2, C29.2, C30.2, D11.C, D14.C, D15.GND, J11.1, J12.GND, J12.GND2, J13.1, J14.6, J14.GND1, J14.GND2, J14.GND3, J14.GND4, J14.GND5, J14.GND6, J15.25, JP9.1, R22.1, R24.1, R30.1, R31.1, S5.1, S5.2, S6.1, S6.2, U13.2, U14.1, U15.1, U15.4, U15.6, U15.9, U16.2, U17.2, U18.1, U18.15, U18.38, U18.GND1, U18.GNDT1, U18.GNDT2, U18.GNDT3, U18.GNDT4, U18.GNDT5, U18.GNDT6, U18.GNDT7, U18.GNDT8
GND3: C31.2, C32.2, C33.2, C34.2, C35.2, C36.2, C37.2, C38.2, C39.2, C40.2, D17.C, D19.C, D20.GND, J16.1, J17.GND, J17.GND2, J18.1, J19.6, J19.GND1, J19.GND2, J19.GND3, J19.GND4, J19.GND5, J19.GND6, J20.25, JP12.1, R33.1, R36.1, R42.1, R43.1, S7.1, S7.2, S8.1, S8.2, U19.2, U20.1, U21.1, U21.4, U21.6, U21.9, U22.2, U23.2, U24.1, U24.15, U24.38, U24.GND1, U24.GNDT1, U24.GNDT2, U24.GNDT3, U24.GNDT4, U24.GNDT5, U24.GNDT6, U24.GNDT7, U24.GNDT8
GND4: C41.2, C42.2, C43.2, C44.2, C45.2, C46.2, C47.2, C48.2, C49.2, C50.2, D22.C, D24.C, D25.GND, J21.1, J22.GND, J22.GND2, J23.1, J24.6, J24.GND1, J24.GND2, J24.GND3, J24.GND4, J24.GND5, J24.GND6, J25.25, JP15.1, R45.1, R47.1, R53.1, R54.1, S9.1, S9.2, S10.1, S10.2, U25.2, U26.1, U27.1, U27.4, U27.6, U27.9, U28.2, U29.2, U30.1, U30.15, U30.38, U30.GND1, U30.GNDT1, U30.GNDT2, U30.GNDT3, U30.GNDT4, U30.GNDT5, U30.GNDT6, U30.GNDT7, U30.GNDT8
GND5: C51.2, C52.2, C53.2, C54.2, C55.2, C56.2, C57.2, C58.2, C59.2, C60.2, D27.C, D29.C, D30.GND, J26.1, J27.GND, J27.GND2, J28.1, J29.6, J29.GND1, J29.GND2, J29.GND3, J29.GND4, J29.GND5, J29.GND6, J30.25, JP18.1, R56.1, R58.1, R64.1, R65.1, S11.1, S11.2, S12.1, S12.2, U31.2, U32.1, U33.1, U33.4, U33.6, U33.9, U34.2, U35.2, U36.1, U36.15, U36.38, U36.GND1, U36.GNDT1, U36.GNDT2, U36.GNDT3, U36.GNDT4, U36.GNDT5, U36.GNDT6, U36.GNDT7, U36.GNDT8
GND6: C61.2, C62.2, C63.2, C64.2, C65.2, C66.2, C67.2, C68.2, C69.2, C70.2, D32.C, D34.C, D35.GND, J31.1, J32.GND, J32.GND2, J33.1, J34.6, J34.GND1, J34.GND2, J34.GND3, J34.GND4, J34.GND5, J34.GND6, J35.25, JP21.1, R67.1, R69.1, R75.1, R76.1, S13.1, S13.2, S14.1, S14.2, U37.2, U38.1, U39.1, U39.4, U39.6, U39.9, U40.2, U41.2, U42.1, U42.15, U42.38, U42.GND1, U42.GNDT1, U42.GNDT2, U42.GNDT3, U42.GNDT4, U42.GNDT5, U42.GNDT6, U42.GNDT7, U42.GNDT8
GND7: C71.2, C72.2, C73.2, C74.2, C75.2, C76.2, C77.2, C78.2, C79.2, C80.2, D37.C, D39.C, D40.GND, J36.1, J37.GND, J37.GND2, J38.1, J39.6, J39.GND1, J39.GND2, J39.GND3, J39.GND4, J39.GND5, J39.GND6, J40.25, JP24.1, R78.1, R80.1, R86.1, R87.1, S15.1, S15.2, S16.1, S16.2, U43.2, U44.1, U45.1, U45.4, U45.6, U45.9, U46.2, U47.2, U48.1, U48.15, U48.38, U48.GND1, U48.GNDT1, U48.GNDT2, U48.GNDT3, U48.GNDT4, U48.GNDT5, U48.GNDT6, U48.GNDT7, U48.GNDT8
GND8: C81.2, C82.2, C83.2, C84.2, C85.2, C86.2, C87.2, C88.2, C89.2, C90.2, D42.C, D44.C, D45.GND, J41.1, J42.GND, J42.GND2, J43.1, J44.6, J44.GND1, J44.GND2, J44.GND3, J44.GND4, J44.GND5, J44.GND6, J45.25, JP27.1, R89.1, R91.1, R97.1, R98.1, S17.1, S17.2, S18.1, S18.2, U49.2, U50.1, U51.1, U51.4, U51.6, U51.9, U52.2, U53.2, U54.1, U54.15, U54.38, U54.GND1, U54.GNDT1, U54.GNDT2, U54.GNDT3, U54.GNDT4, U54.GNDT5, U54.GNDT6, U54.GNDT7, U54.GNDT8
GND9: C91.2, C92.2, C93.2, C94.2, C95.2, C96.2, C97.2, C98.2, C99.2, C100.2, D47.C, D49.C, D50.GND, J46.1, J47.GND, J47.GND2, J48.1, J49.6, J49.GND1, J49.GND2, J49.GND3, J49.GND4, J49.GND5, J49.GND6, J50.25, JP30.1, R100.1, R102.1, R108.1, R109.1, S19.1, S19.2, S20.1, S20.2, U55.2, U56.1, U57.1, U57.4, U57.6, U57.9, U58.2, U59.2, U60.1, U60.15, U60.38, U60.GND1, U60.GNDT1, U60.GNDT2, U60.GNDT3, U60.GNDT4, U60.GNDT5, U60.GNDT6, U60.GNDT7, U60.GNDT8
GND10: C101.2, C102.2, C103.2, C104.2, C105.2, C106.2, C107.2, C108.2, C109.2, C110.2, D52.C, D54.C, D55.GND, J51.1, J52.GND, J52.GND2, J53.1, J54.6, J54.GND1, J54.GND2, J54.GND3, J54.GND4, J54.GND5, J54.GND6, J55.25, JP33.1, R111.1, R113.1, R119.1, R120.1, S21.1, S21.2, S22.1, S22.2, U61.2, U62.1, U63.1, U63.4, U63.6, U63.9, U64.2, U65.2, U66.1, U66.15, U66.38, U66.GND1, U66.GNDT1, U66.GNDT2, U66.GNDT3, U66.GNDT4, U66.GNDT5, U66.GNDT6, U66.GNDT7, U66.GNDT8
GND11: C111.2, C112.2, C113.2, C114.2, C115.2, C116.2, C117.2, C118.2, C119.2, C120.2, D57.C, D59.C, D60.GND, J56.1, J57.GND, J57.GND2, J58.1, J59.6, J59.GND1, J59.GND2, J59.GND3, J59.GND4, J59.GND5, J59.GND6, J60.25, JP36.1, R122.1, R124.1, R130.1, R131.1, S23.1, S23.2, S24.1, S24.2, U67.2, U68.1, U69.1, U69.4, U69.6, U69.9, U70.2, U71.2, U72.1, U72.15, U72.38, U72.GND1, U72.GNDT1, U72.GNDT2, U72.GNDT3, U72.GNDT4, U72.GNDT5, U72.GNDT6, U72.GNDT7, U72.GNDT8
unnamed: JP1.1, R34.1
unnamed: D3.A, R4.2
unnamed: D5.DO, TP2.1
unnamed: JP2.1, R3.1
unnamed: J1.B5, R9.2
unnamed: J1.A5, R10.2
unnamed: D1.C, U1.1
unnamed: J1.SHLD1, J1.SHLD2, J1.SHLD3, J1.SHLD4, JP3.2
unnamed: R11.2, U6.5
unnamed: D6.A, R15.2
unnamed: J7.B5, R19.2
unnamed: J7.A5, R20.2
unnamed: R6.2, U1.5
unnamed: D8.A, R21.2
unnamed: JP4.1, R21.1
unnamed: D9.DO, TP6.1
unnamed: JP5.1, R5.1
unnamed: D2.C, U6.1
unnamed: J7.SHLD1, J7.SHLD2, J7.SHLD3, J7.SHLD4, JP6.2
unnamed: R24.2, U13.5
unnamed: D11.A, R28.2
unnamed: J12.B5, R30.2
unnamed: J12.A5, R31.2
unnamed: D14.A, R32.2
unnamed: JP7.1, R32.1
unnamed: D15.DO, TP10.1
unnamed: D12.A, R34.2
unnamed: JP8.1, R23.1
unnamed: D10.C, U13.1
unnamed: J12.SHLD1, J12.SHLD2, J12.SHLD3, J12.SHLD4, JP9.2
unnamed: R36.2, U19.5
unnamed: D17.A, R40.2
unnamed: J17.B5, R42.2
unnamed: J17.A5, R43.2
unnamed: D19.A, R44.2
unnamed: JP10.1, R44.1
unnamed: D20.DO, TP14.1
unnamed: JP11.1, R35.1
unnamed: D16.C, U19.1
unnamed: J17.SHLD1, J17.SHLD2, J17.SHLD3, J17.SHLD4, JP12.2
unnamed: R47.2, U25.5
unnamed: D22.A, R51.2
unnamed: J22.B5, R53.2
unnamed: J22.A5, R54.2
unnamed: D24.A, R55.2
unnamed: JP13.1, R55.1
unnamed: D25.DO, TP18.1
unnamed: JP14.1, R46.1
unnamed: D21.C, U25.1
unnamed: J22.SHLD1, J22.SHLD2, J22.SHLD3, J22.SHLD4, JP15.2
unnamed: R58.2, U31.5
unnamed: D27.A, R62.2
unnamed: J27.B5, R64.2
unnamed: J27.A5, R65.2
unnamed: D29.A, R66.2
unnamed: JP16.1, R66.1
unnamed: D30.DO, TP22.1
unnamed: JP17.1, R57.1
unnamed: D26.C, U31.1
unnamed: J27.SHLD1, J27.SHLD2, J27.SHLD3, J27.SHLD4, JP18.2
unnamed: R69.2, U37.5
unnamed: D32.A, R73.2
unnamed: J32.B5, R75.2
unnamed: J32.A5, R76.2
unnamed: D34.A, R77.2
unnamed: JP19.1, R77.1
unnamed: D35.DO, TP26.1
unnamed: JP20.1, R68.1
unnamed: D31.C, U37.1
unnamed: J32.SHLD1, J32.SHLD2, J32.SHLD3, J32.SHLD4, JP21.2
unnamed: R80.2, U43.5
unnamed: D37.A, R84.2
unnamed: J37.B5, R86.2
unnamed: J37.A5, R87.2
unnamed: D39.A, R88.2
unnamed: JP22.1, R88.1
unnamed: D40.DO, TP30.1
unnamed: JP23.1, R79.1
unnamed: D36.C, U43.1
unnamed: J37.SHLD1, J37.SHLD2, J37.SHLD3, J37.SHLD4, JP24.2
unnamed: R91.2, U49.5
unnamed: D42.A, R95.2
unnamed: J42.B5, R97.2
unnamed: J42.A5, R98.2
unnamed: D44.A, R99.2
unnamed: JP25.1, R99.1
unnamed: D45.DO, TP34.1
unnamed: JP26.1, R90.1
unnamed: D41.C, U49.1
unnamed: J42.SHLD1, J42.SHLD2, J42.SHLD3, J42.SHLD4, JP27.2
unnamed: R102.2, U55.5
unnamed: D47.A, R106.2
unnamed: J47.B5, R108.2
unnamed: J47.A5, R109.2
unnamed: D49.A, R110.2
unnamed: JP28.1, R110.1
unnamed: D50.DO, TP38.1
unnamed: JP29.1, R101.1
unnamed: D46.C, U55.1
unnamed: J47.SHLD1, J47.SHLD2, J47.SHLD3, J47.SHLD4, JP30.2
unnamed: R113.2, U61.5
unnamed: D52.A, R117.2
unnamed: J52.B5, R119.2
unnamed: J52.A5, R120.2
unnamed: D54.A, R121.2
unnamed: JP31.1, R121.1
unnamed: D55.DO, TP42.1
unnamed: JP32.1, R112.1
unnamed: D51.C, U61.1
unnamed: J52.SHLD1, J52.SHLD2, J52.SHLD3, J52.SHLD4, JP33.2
unnamed: R124.2, U67.5
unnamed: D57.A, R128.2
unnamed: J57.B5, R130.2
unnamed: J57.A5, R131.2
unnamed: D59.A, R132.2
unnamed: JP34.1, R132.1
unnamed: D60.DO, TP46.1
unnamed: JP35.1, R123.1
unnamed: D56.C, U67.1
unnamed: J57.SHLD1, J57.SHLD2, J57.SHLD3, J57.SHLD4, JP36.2
QWIIC_PWR: C3.1, J3.2, U5.5
QWIIC_PWR1: C17.1, J6.2, U11.5
QWIIC_PWR2: C28.1, J11.2, U17.5
QWIIC_PWR3: C38.1, J16.2, U23.5
QWIIC_PWR4: C48.1, J21.2, U29.5
QWIIC_PWR5: C58.1, J26.2, U35.5
QWIIC_PWR6: C68.1, J31.2, U41.5
QWIIC_PWR7: C78.1, J36.2, U47.5
QWIIC_PWR8: C88.1, J41.2, U53.5
QWIIC_PWR9: C98.1, J46.2, U59.5
QWIIC_PWR10: C108.1, J51.2, U65.5
QWIIC_PWR11: C118.1, J56.2, U71.5
RTS-10K: Q2.2, R18.2
RTS-10K1: Q1.2, R13.2
RTS-10K2: Q5.2, R26.2
RTS-10K3: Q7.2, R38.2
RTS-10K4: Q9.2, R49.2
RTS-10K5: Q11.2, R60.2
RTS-10K6: Q13.2, R71.2
RTS-10K7: Q15.2, R82.2
RTS-10K8: Q17.2, R93.2
RTS-10K9: Q19.2, R104.2
RTS-10K10: Q21.2, R115.2
RTS-10K11: Q23.2, R126.2
TP_EN: J5.11, R8.2, U3.3
TP_EN1: J10.11, R16.2, U10.3
TP_EN2: J15.11, R29.2, U16.3
TP_EN3: J20.11, R41.2, U22.3
TP_EN4: J25.11, R52.2, U28.3
TP_EN5: J30.11, R63.2, U34.3
TP_EN6: J35.11, R74.2, U40.3
TP_EN7: J40.11, R85.2, U46.3
TP_EN8: J45.11, R96.2, U52.3
TP_EN9: J50.11, R107.2, U58.3
TP_EN10: J55.11, R118.2, U64.3
TP_EN11: J60.11, R129.2, U70.3
VIN: C7.1, D4.C, Q3.2, R8.1, U3.1, U5.1
VIN1: C8.1, D7.C, Q4.2, R16.1, U10.1, U11.1
VIN2: C21.1, D13.C, Q6.2, R29.1, U16.1, U17.1
VIN3: C31.1, D18.C, Q8.2, R41.1, U22.1, U23.1
VIN4: C41.1, D23.C, Q10.2, R52.1, U28.1, U29.1
VIN5: C51.1, D28.C, Q12.2, R63.1, U34.1, U35.1
VIN6: C61.1, D33.C, Q14.2, R74.1, U40.1, U41.1
VIN7: C71.1, D38.C, Q16.2, R85.1, U46.1, U47.1
VIN8: C81.1, D43.C, Q18.2, R96.1, U52.1, U53.1
VIN9: C91.1, D48.C, Q20.2, R107.1, U58.1, U59.1
VIN10: C101.1, D53.C, Q22.2, R118.1, U64.1, U65.1
VIN11: C111.1, D58.C, Q24.2, R129.1, U70.1, U71.1
V_BATT: C6.1, C15.1, J4.2, J5.12, Q3.3, U1.3, U4.2, U4.3
V_BATT1: C11.1, C16.1, J8.2, J10.12, Q4.3, U6.3, U9.2, U9.3
V_BATT2: C23.1, C27.1, J13.2, J15.12, Q6.3, U13.3, U15.2, U15.3
V_BATT3: C33.1, C37.1, J18.2, J20.12, Q8.3, U19.3, U21.2, U21.3
V_BATT4: C43.1, C47.1, J23.2, J25.12, Q10.3, U25.3, U27.2, U27.3
V_BATT5: C53.1, C57.1, J28.2, J30.12, Q12.3, U31.3, U33.2, U33.3
V_BATT6: C63.1, C67.1, J33.2, J35.12, Q14.3, U37.3, U39.2, U39.3
V_BATT7: C73.1, C77.1, J38.2, J40.12, Q16.3, U43.3, U45.2, U45.3
V_BATT8: C83.1, C87.1, J43.2, J45.12, Q18.3, U49.3, U51.2, U51.3
V_BATT9: C93.1, C97.1, J48.2, J50.12, Q20.3, U55.3, U57.2, U57.3
V_BATT10: C103.1, C107.1, J53.2, J55.12, Q22.3, U61.3, U63.2, U63.3
V_BATT11: C113.1, C117.1, J58.2, J60.12, Q24.3, U67.3, U69.2, U69.3
V_USB: C19.1, D4.A, J1.VBUS1, J1.VBUS2, J5.10, JP2.2, Q3.1, R7.2, U1.4
V_USB1: C12.1, D7.A, J7.VBUS1, J7.VBUS2, J10.10, JP5.2, Q4.1, R1.2, U6.4
V_USB2: C24.1, D13.A, J12.VBUS1, J12.VBUS2, J15.10, JP8.2, Q6.1, R22.2, U13.4
V_USB3: C34.1, D18.A, J17.VBUS1, J17.VBUS2, J20.10, JP11.2, Q8.1, R33.2, U19.4
V_USB4: C44.1, D23.A, J22.VBUS1, J22.VBUS2, J25.10, JP14.2, Q10.1, R45.2, U25.4
V_USB5: C54.1, D28.A, J27.VBUS1, J27.VBUS2, J30.10, JP17.2, Q12.1, R56.2, U31.4
V_USB6: C64.1, D33.A, J32.VBUS1, J32.VBUS2, J35.10, JP20.2, Q14.1, R67.2, U37.4
V_USB7: C74.1, D38.A, J37.VBUS1, J37.VBUS2, J40.10, JP23.2, Q16.1, R78.2, U43.4
V_USB8: C84.1, D43.A, J42.VBUS1, J42.VBUS2, J45.10, JP26.2, Q18.1, R89.2, U49.4
V_USB9: C94.1, D48.A, J47.VBUS1, J47.VBUS2, J50.10, JP29.2, Q20.1, R100.2, U55.4
V_USB10: C104.1, D53.A, J52.VBUS1, J52.VBUS2, J55.10, JP32.2, Q22.1, R111.2, U61.4
V_USB11: C114.1, D58.A, J57.VBUS1, J57.VBUS2, J60.10, JP35.2, Q24.1, R122.2, U67.4
